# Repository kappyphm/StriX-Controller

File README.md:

# StriX Controller

The StriX Controller is a custom-designed game controller for flight simulation games, featuring dual analog joysticks, four switches, and a user-friendly USB Type-C interface. Built with an AtMega32U4 microcontroller, it supports HID protocol for plug-and-play compatibility. The controller includes an OLED display for real-time feedback via I2C and supports configuration through a rotary encoder (KY-040) or a software driver. Designed with modularity in mind, it includes an SPI interface for potential integration with the StriX UAV project via an NRF24L01 module.

## Features

- **Dual Analog Joysticks**: Precise control for flight simulation games.
- **Four Switches**: Additional input options for customizable actions.
- **USB Type-C Connectivity**: Modern, reliable connection for data and firmware updates.
- **AtMega32U4 MCU**: Provides native HID support for seamless integration with PCs.
- **OLED Display**: Displays real-time information via I2C communication.
- **Configurability**: Adjust settings using a KY-040 rotary encoder or a software driver.
- **SPI Interface**: Reserved pins for NRF24L01 module, enabling future StriX UAV integration.
- **Firmware Updates**: Update firmware via USB Type-C using standard tools like avrdude.

## Project Structure

- **Hardware/**: Contains KiCad project files for the controller’s PCB design and schematics.
- **Software/**: Placeholder for the software driver
- **Firmware/**: PlatformIO project for the AtMega32U4, including firmware code for controller functionality.

## Hardware Requirements

- AtMega32U4 microcontroller
- Dual analog joysticks
- Four switches
- USB Type-C port
- OLED display (I2C-compatible)
- KY-040 rotary encoder
- Optional: NRF24L01 module for future wireless expansion

## Setup Instructions

1. **Hardware Setup**:
   - Assemble the controller using the KiCad schematics in the `Hardware/` folder.
   - Ensure proper connections for the AtMega32U4, joysticks, switches, OLED, and KY-040.
2. **Firmware Installation**:
   - Clone the repository and open the `Firmware/` folder in PlatformIO.
   - Build and upload the firmware to the AtMega32U4 via USB Type-C using a compatible tool (e.g., avrdude).
3. **Software Driver**:
   - (TBD) Develop or install the driver from the `Software/` folder to configure controller settings.
4. **Testing**:
   - Connect the controller to a PC via USB Type-C.
   - Verify HID functionality and OLED display output.
   - Test joystick, switch, and KY-040 inputs in a flight simulation game.

## Firmware Updates

To update the firmware:

1. Connect the controller to a PC via USB Type-C.
2. Use a tool like avrdude to flash the updated firmware from the `Firmware/` folder.
3. Follow the PlatformIO documentation for detailed build and upload instructions.

## Future Expansion

The StriX Controller is designed for future integration with the StriX UAV project. The reserved SPI pins allow connection to an NRF24L01 module, enabling the controller to function as a transmitter (TX) for UAV control.

## Contributing

Contributions are welcome! Please fork the repository, make changes, and submit a pull request. Ensure your code follows the project’s coding standards and includes appropriate documentation.

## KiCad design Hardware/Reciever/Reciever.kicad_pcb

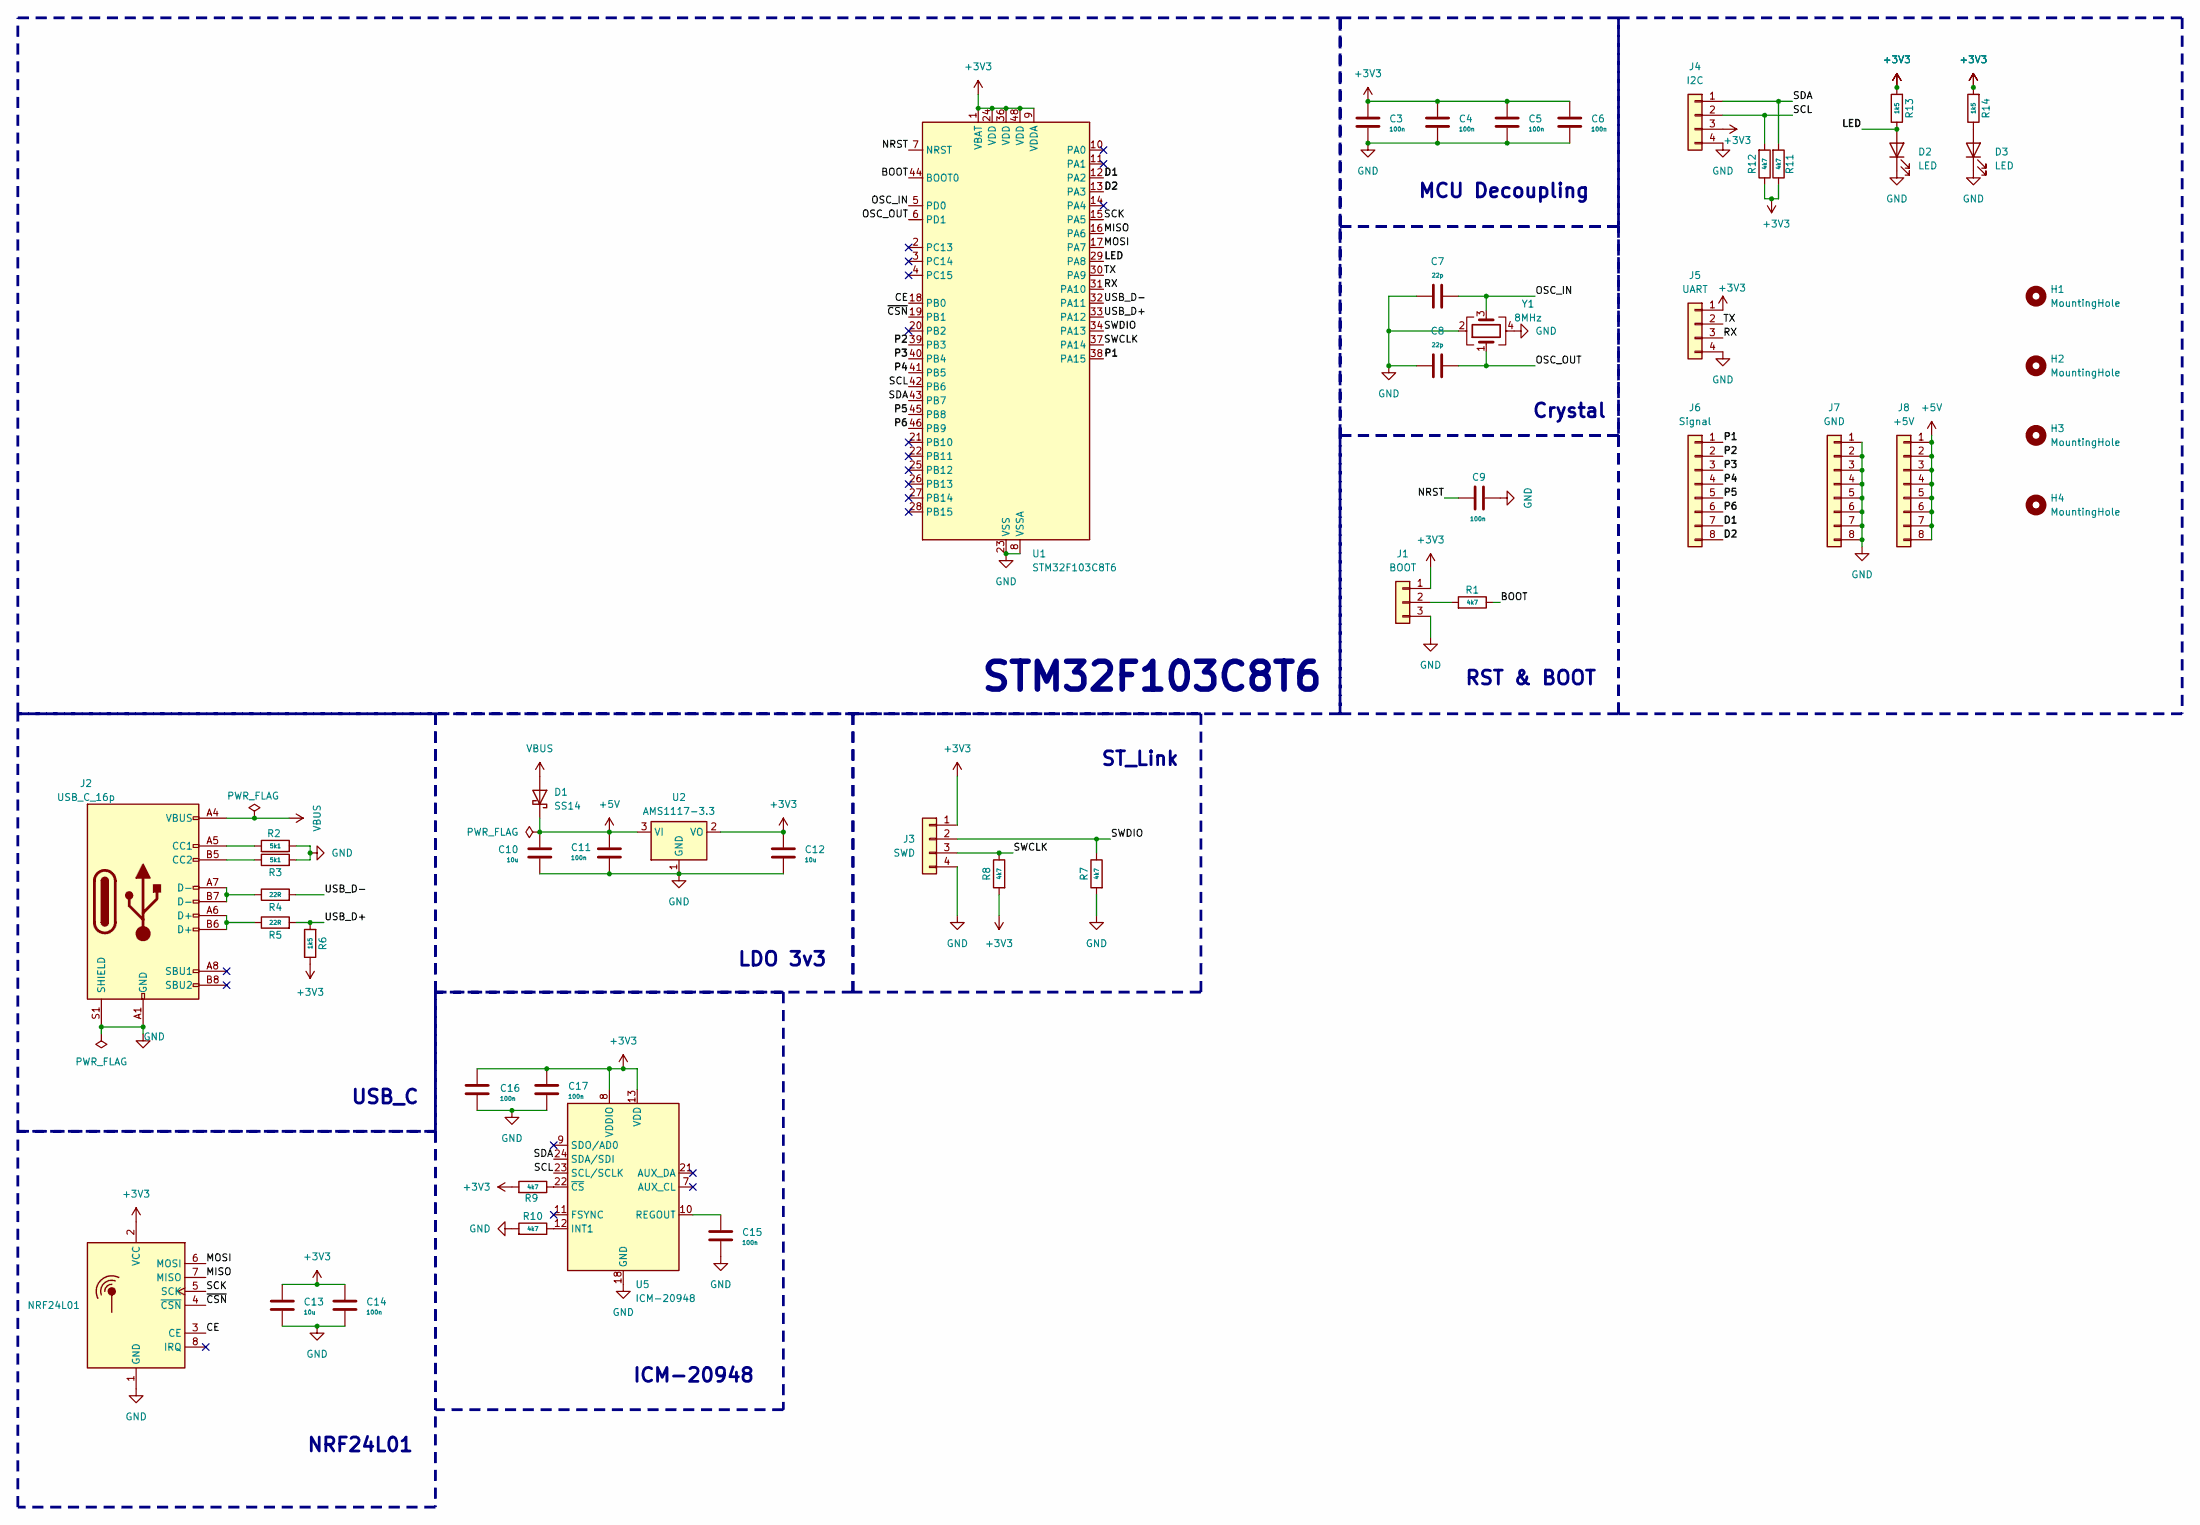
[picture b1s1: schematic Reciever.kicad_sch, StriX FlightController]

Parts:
C3, C4, C5, C6, C9, C11, C14, C15, C16, C17: 100n; C_0603_1608Metric
C7, C8: 22p; C_0603_1608Metric
C10, C12, C13: 10u; C_0603_1608Metric
D1: SS14; D_SMA
D2, D3: LED; LED_1206_3216Metric
H1, H2, H3, H4: MountingHole; MountingHole_2.5mm
J1: BOOT; PinHeader_1x03_P2.54mm_Vertical
J2: USB_C_16p; USB_C_Receptacle_HRO_TYPE-C-31-M-12
J3: SWD; PinHeader_1x04_P2.54mm_Vertical
J4: I2C; PinHeader_1x04_P2.54mm_Vertical
J5: UART; PinHeader_1x04_P2.54mm_Vertical
J6: Signal; PinHeader_1x08_P2.54mm_Vertical
J7: GND; PinHeader_1x08_P2.54mm_Vertical
J8: +5V; PinHeader_1x08_P2.54mm_Vertical
R1, R7, R8, R9, R10, R11, R12: 4k7; R_0603_1608Metric
R2, R3: 5k1; R_0603_1608Metric
R4, R5: 22R; R_0603_1608Metric
R6, R13, R14: 1k5; R_0603_1608Metric
U1: STM32F103C8T6; LQFP-48_7x7mm_P0.5mm
U2: AMS1117-3.3; SOT-223-3_TabPin2
U4: NRF24L01; NRF24L01_PA_LNA
U5: ICM-20948; InvenSense_QFN-24_3x3mm_P0.4mm
Y1: 8MHz; Crystal_SMD_5032-4Pin_5.0x3.2mm

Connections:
+3V3: C3.1, C4.1, C5.1, C6.1, C12.1, C13.1, C14.1, C16.1, C17.1, J1.1, J3.1, J4.3, J5.1, R6.1, R8.2, R9.2, R11.1, R12.1, R13.2, R14.2, U1.1 (VBAT), U1.9 (VDDA), U1.24 (VDD), U1.36 (VDD), U1.48 (VDD), U2.2 (VO), U4.2 (VCC), U5.8 (VDDIO), U5.13 (VDD)
+5V: C10.1, C11.1, D1.1 (K), J8.1, J8.2, J8.3, J8.4, J8.5, J8.6, J8.7, J8.8, U2.3 (VI)
/BOOT: R1.1, U1.44 (BOOT0)
/CE: U1.18 (PB0), U4.3 (CE)
/D1: J6.7, U1.12 (PA2)
/D2: J6.8, U1.13 (PA3)
/LED: D2.2 (A), R13.1, U1.29 (PA8)
/MISO: U1.16 (PA6), U4.7 (MISO)
/MOSI: U1.17 (PA7), U4.6 (MOSI)
/NRST: C9.1, U1.7 (NRST)
/OSC_IN: C7.2, U1.5 (PD0), Y1.3
/OSC_OUT: C8.2, U1.6 (PD1), Y1.1
/P1: J6.1, U1.38 (PA15)
/P2: J6.2, U1.39 (PB3)
/P3: J6.3, U1.40 (PB4)
/P4: J6.4, U1.41 (PB5)
/P5: J6.5, U1.45 (PB8)
/P6: J6.6, U1.46 (PB9)
/RX: J5.3, U1.31 (PA10)
/SCK: U1.15 (PA5), U4.5 (SCK)
/SCL: J4.2, R12.2, U1.42 (PB6), U5.23 (SCL/SCLK)
/SDA: J4.1, R11.2, U1.43 (PB7), U5.24 (SDA/SDI)
/SWCLK: J3.3, R8.1, U1.37 (PA14)
/SWDIO: J3.2, R7.1, U1.34 (PA13)
/TX: J5.2, U1.30 (PA9)
/USB_D+: R5.2, R6.2, U1.33 (PA12)
/USB_D-: R4.2, U1.32 (PA11)
/~CSN: U1.19 (PB1), U4.4 (~CSN)
GND: C3.2, C4.2, C5.2, C6.2, C7.1, C8.1, C9.2, C10.2, C11.2, C12.2, C13.2, C14.2, C15.2, C16.2, C17.2, D2.1 (K), D3.1 (K), J1.3, J2.A1 (GND), J2.A12 (GND), J2.B1 (GND), J2.B12 (GND), J2.S1 (SHIELD), J3.4, J4.4, J5.4, J7.1, J7.2, J7.3, J7.4, J7.5, J7.6, J7.7, J7.8, R2.2, R3.2, R7.2, R10.2, U1.8 (VSSA), U1.23 (VSS), U1.35 (VSS), U1.47 (VSS), U2.1 (GND), U4.1 (GND), U5.18 (GND), U5.20 (GND), Y1.2, Y1.4
unnamed: D3.2 (A), R14.1
unnamed: J1.2, R1.2
unnamed: J2.A5 (CC1), R2.1
unnamed: J2.B5 (CC2), R3.1
unnamed: J2.A6 (D+), J2.B6 (D+), R5.1
unnamed: J2.A7 (D-), J2.B7 (D-), R4.1
unnamed: R10.1, U5.12 (INT1)
unnamed: C15.1, U5.10 (REGOUT)
unnamed: R9.1, U5.22 (~CS)
VBUS: D1.2 (A), J2.A4 (VBUS), J2.A9 (VBUS), J2.B4 (VBUS), J2.B9 (VBUS)

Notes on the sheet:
ST_Link
Crystal
LDO 3v3
USB_C
ICM-20948
RST & BOOT
NRF24L01
STM32F103C8T6
MCU Decoupling

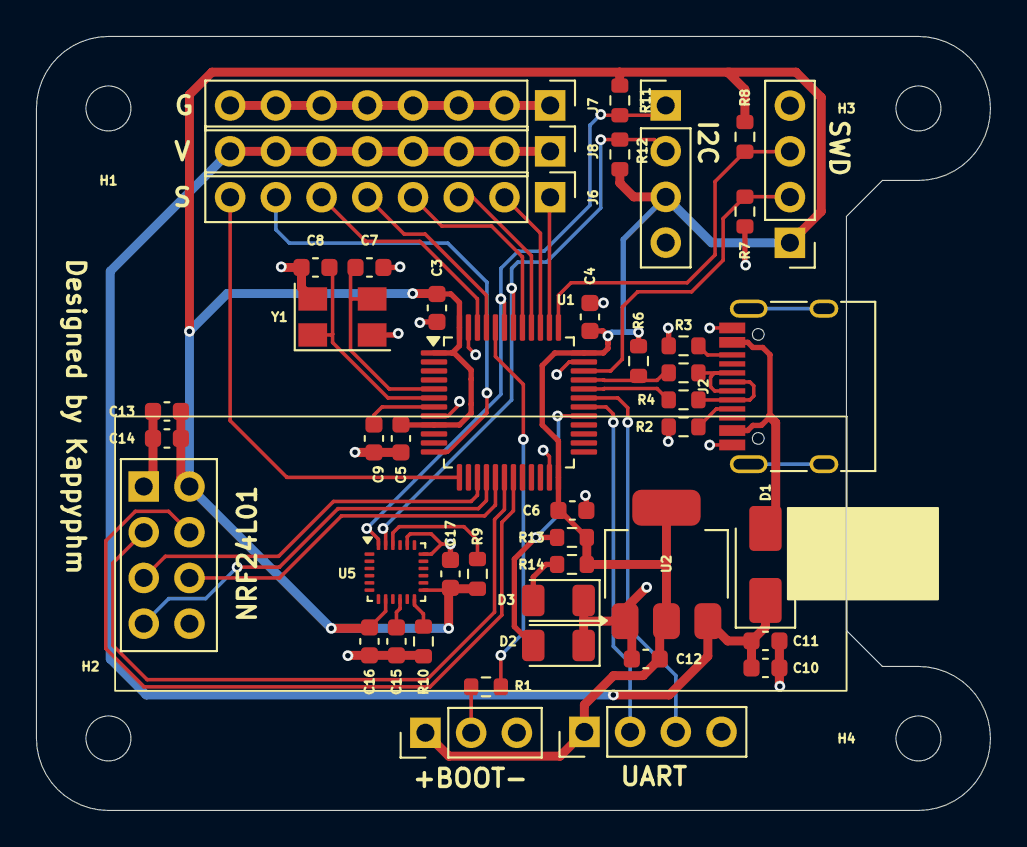
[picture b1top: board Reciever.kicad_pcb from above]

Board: 2 copper layers, 53.0 x 43.0 mm, 49 parts (0 on the bottom side), 39 nets.

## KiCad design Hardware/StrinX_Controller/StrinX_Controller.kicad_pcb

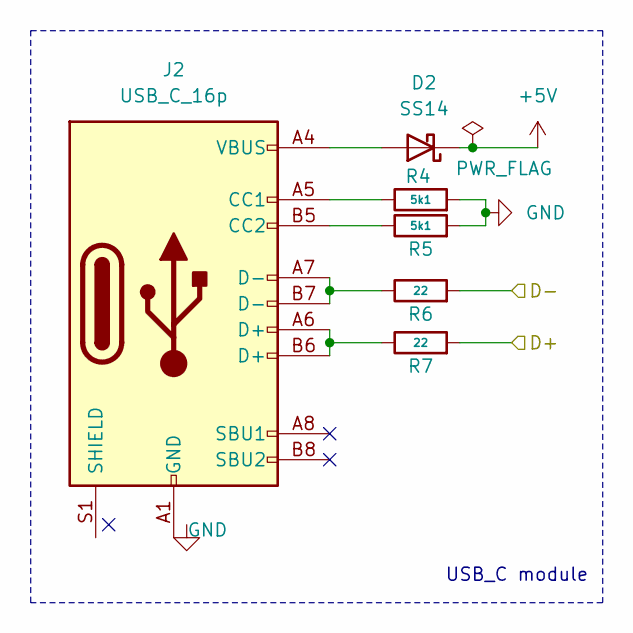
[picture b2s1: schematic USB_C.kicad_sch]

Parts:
D2: SS14; D_SMA
J2: USB_C_16p
R4, R5: 5k1
R6, R7: 22

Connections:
+5V: D2.1 (K); also elsewhere on the board
/AT32u4/D+: R7.2; also elsewhere on the board
/AT32u4/D-: R6.2; also elsewhere on the board
unnamed: D2.2 (A), J2.A4 (VBUS), J2.A9 (VBUS), J2.B4 (VBUS), J2.B9 (VBUS)
unnamed: J2.A5 (CC1), R4.1
unnamed: J2.B5 (CC2), R5.1
unnamed: J2.A6 (D+), J2.B6 (D+), R7.1
unnamed: J2.A7 (D-), J2.B7 (D-), R6.1

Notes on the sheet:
USB_C module

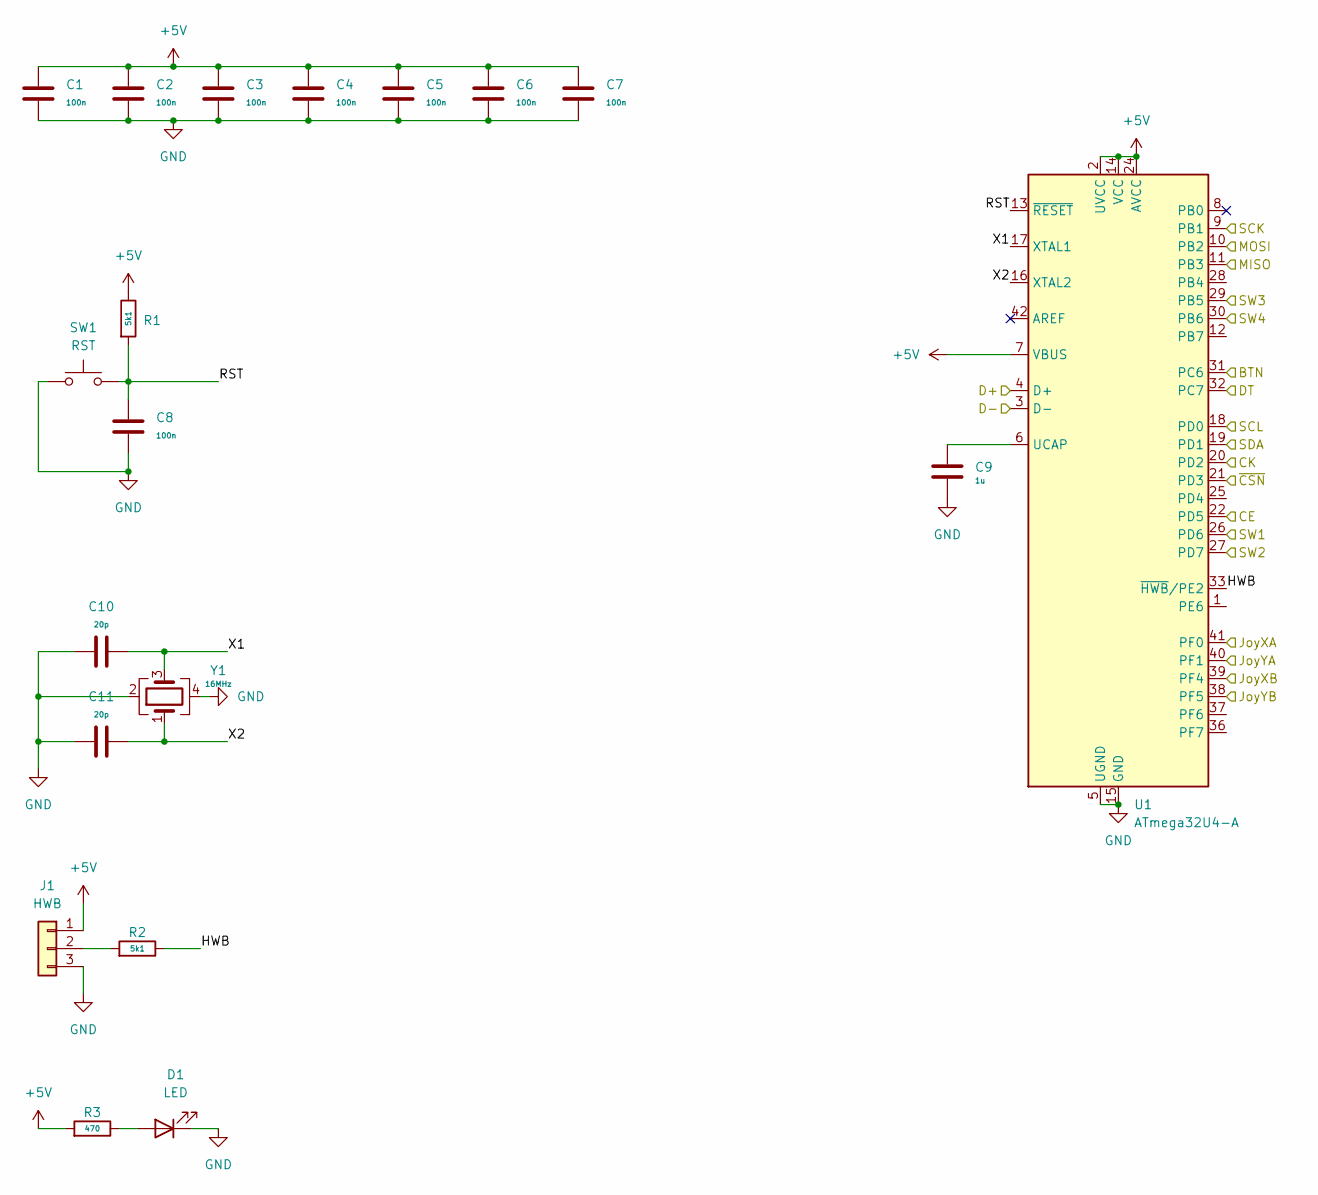
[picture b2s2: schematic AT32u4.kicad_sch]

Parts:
C1, C2, C3, C4, C5, C6, C7, C8: 100n; C_0603_1608Metric
C9: 1u; C_0603_1608Metric
C10, C11: 20p; C_0603_1608Metric
D1: LED; LED_1206_3216Metric
J1: HWB; PinHeader_1x03_P2.54mm_Vertical
R1, R2: 5k1; R_0603_1608Metric
R3: 470; R_0603_1608Metric
SW1: RST; SW_PUSH_6mm_H4.3mm
U1: ATmega32U4-A; TQFP-44_10x10mm_P0.8mm
Y1: 16MHz; Crystal_SMD_7050-4Pin_7.0x5.0mm

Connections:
+5V: C1.1, C2.1, C3.1, C4.1, C5.1, C6.1, C7.1, J1.1, R1.1, R3.2, U1.2 (UVCC), U1.7 (VBUS), U1.14 (VCC), U1.24 (AVCC), U1.34 (VCC), U1.44 (AVCC); also elsewhere on the board
/AT32u4/BTN: U1.31 (PC6); also elsewhere on the board
/AT32u4/CE: U1.22 (PD5); also elsewhere on the board
/AT32u4/CK: U1.20 (PD2); also elsewhere on the board
/AT32u4/D+: U1.4 (D+); also elsewhere on the board
/AT32u4/D-: U1.3 (D-); also elsewhere on the board
/AT32u4/DT: U1.32 (PC7); also elsewhere on the board
/AT32u4/HWB: R2.1, U1.33 (~HWB/PE2)
/AT32u4/JoyXA: U1.41 (PF0); also elsewhere on the board
/AT32u4/JoyXB: U1.39 (PF4); also elsewhere on the board
/AT32u4/JoyYA: U1.40 (PF1); also elsewhere on the board
/AT32u4/JoyYB: U1.38 (PF5); also elsewhere on the board
/AT32u4/MISO: U1.11 (PB3); also elsewhere on the board
/AT32u4/MOSI: U1.10 (PB2); also elsewhere on the board
/AT32u4/RST: C8.1, R1.2, SW1.2, U1.13 (~RESET)
/AT32u4/SCK: U1.9 (PB1); also elsewhere on the board
/AT32u4/SCL: U1.18 (PD0); also elsewhere on the board
/AT32u4/SDA: U1.19 (PD1); also elsewhere on the board
/AT32u4/SW1: U1.26 (PD6); also elsewhere on the board
/AT32u4/SW2: U1.27 (PD7); also elsewhere on the board
/AT32u4/SW3: U1.29 (PB5); also elsewhere on the board
/AT32u4/SW4: U1.30 (PB6); also elsewhere on the board
/AT32u4/X1: C10.2, U1.17 (XTAL1), Y1.3
/AT32u4/X2: C11.2, U1.16 (XTAL2), Y1.1
/AT32u4/~CSN: U1.21 (PD3); also elsewhere on the board
unnamed: D1.2 (A), R3.1
unnamed: J1.2, R2.2
unnamed: C9.2, U1.6 (UCAP)

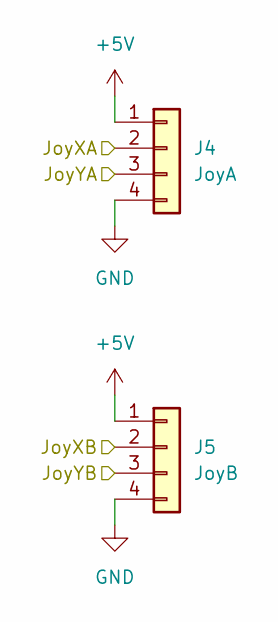
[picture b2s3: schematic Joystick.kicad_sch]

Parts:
J4: JoyA; PinHeader_1x04_P2.54mm_Vertical
J5: JoyB; PinHeader_1x04_P2.54mm_Vertical

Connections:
+5V: J4.1, J5.1; also elsewhere on the board
/AT32u4/JoyXA: J4.2; also elsewhere on the board
/AT32u4/JoyXB: J5.2; also elsewhere on the board
/AT32u4/JoyYA: J4.3; also elsewhere on the board
/AT32u4/JoyYB: J5.3; also elsewhere on the board

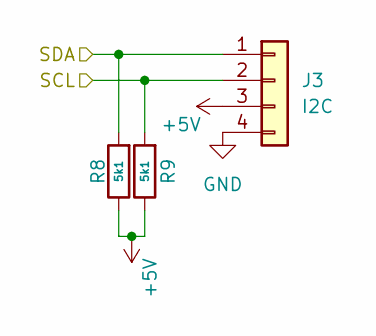
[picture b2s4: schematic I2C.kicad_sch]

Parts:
J3: I2C; PinHeader_1x04_P2.54mm_Vertical
R8, R9: 5k1; R_0603_1608Metric

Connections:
+5V: J3.3, R8.1, R9.1; also elsewhere on the board
/AT32u4/SCL: J3.2, R9.2; also elsewhere on the board
/AT32u4/SDA: J3.1, R8.2; also elsewhere on the board

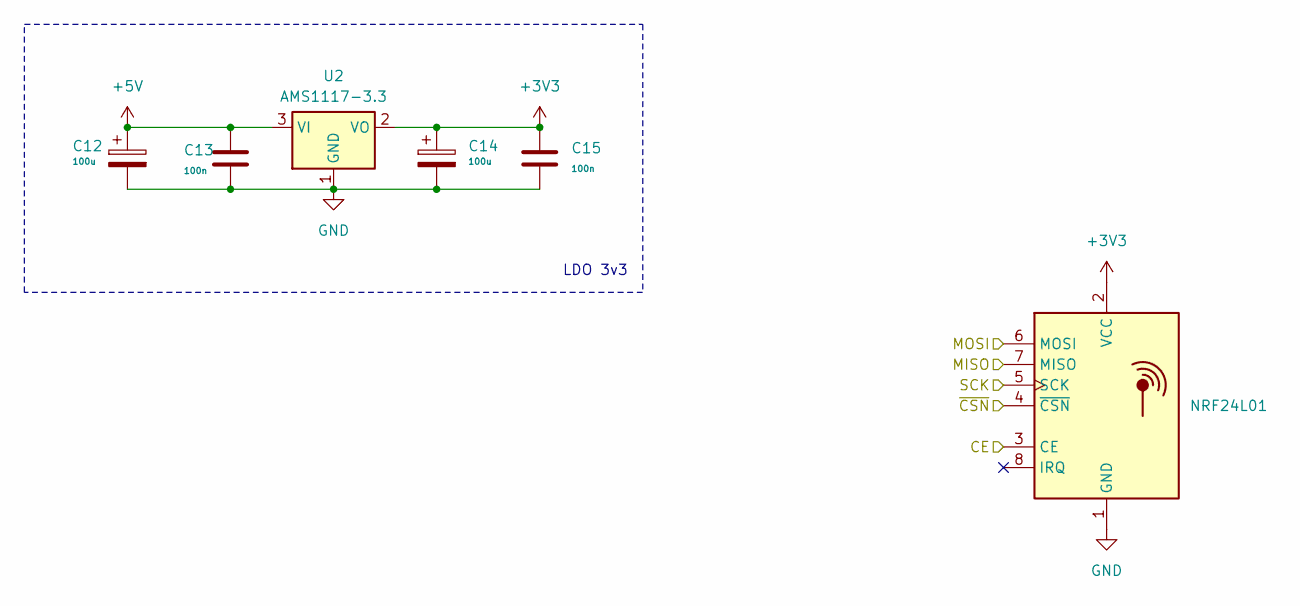
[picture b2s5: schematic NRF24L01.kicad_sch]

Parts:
C12, C14: 100u; C_Radial_D8.0mm_H11.5mm_P3.50mm
C13, C15: 100n; C_0603_1608Metric
U2: AMS1117-3.3; SOT-223-3_TabPin2
U3: NRF24L01; NRF24L01_PA_LNA

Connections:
+3V3: C14.1, C15.1, U2.2 (VO), U3.2 (VCC)
+5V: C12.1, C13.1, U2.3 (VI); also elsewhere on the board
/AT32u4/CE: U3.3 (CE); also elsewhere on the board
/AT32u4/MISO: U3.7 (MISO); also elsewhere on the board
/AT32u4/MOSI: U3.6 (MOSI); also elsewhere on the board
/AT32u4/SCK: U3.5 (SCK); also elsewhere on the board
/AT32u4/~CSN: U3.4 (~CSN); also elsewhere on the board

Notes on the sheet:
LDO 3v3

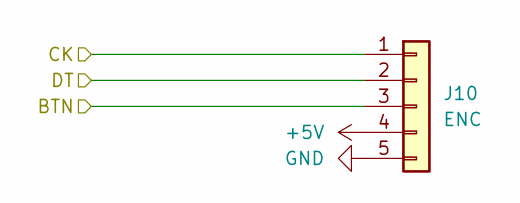
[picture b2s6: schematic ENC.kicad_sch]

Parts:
J10: ENC; PinHeader_1x05_P2.54mm_Vertical

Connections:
+5V: J10.4; also elsewhere on the board
/AT32u4/BTN: J10.3; also elsewhere on the board
/AT32u4/CK: J10.1; also elsewhere on the board
/AT32u4/DT: J10.2; also elsewhere on the board

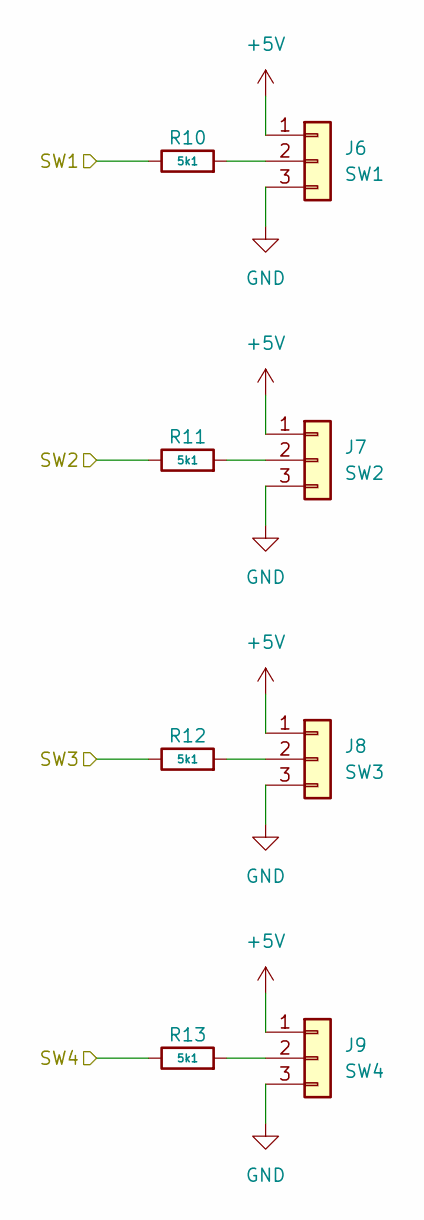
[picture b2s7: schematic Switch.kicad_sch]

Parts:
J6: SW1; PinHeader_1x03_P2.54mm_Vertical
J7: SW2; PinHeader_1x03_P2.54mm_Vertical
J8: SW3; PinHeader_1x03_P2.54mm_Vertical
J9: SW4; PinHeader_1x03_P2.54mm_Vertical
R10, R11, R12, R13: 5k1; R_0603_1608Metric

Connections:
+5V: J6.1, J7.1, J8.1, J9.1; also elsewhere on the board
/AT32u4/SW1: R10.1; also elsewhere on the board
/AT32u4/SW2: R11.1; also elsewhere on the board
/AT32u4/SW3: R12.1; also elsewhere on the board
/AT32u4/SW4: R13.1; also elsewhere on the board
unnamed: J6.2, R10.2
unnamed: J7.2, R11.2
unnamed: J8.2, R12.2
unnamed: J9.2, R13.2

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
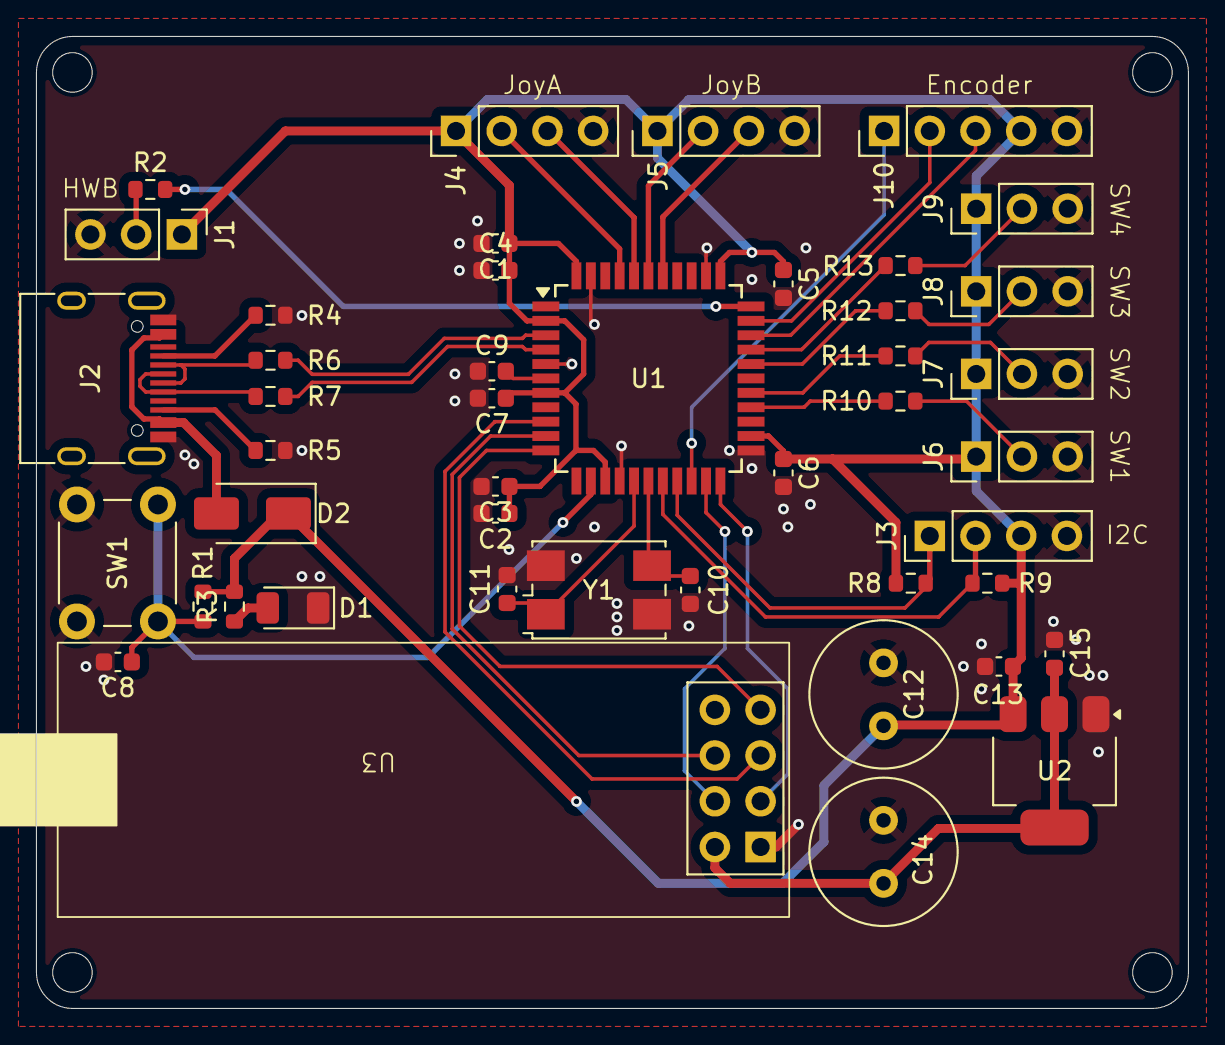
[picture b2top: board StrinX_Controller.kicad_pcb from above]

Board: 2 copper layers, 64.0 x 54.0 mm, 45 parts (0 on the bottom side), 39 nets.

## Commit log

2025-07-29 init hardware
2025-07-29 Add ATmega32U4 schematic and update project files
    Added AT32u4.kicad_sch schematic for the ATmega32U4 microcontroller. Updated StrinX_Controller.kicad_pro and StrinX_Controller.kicad_sch to include the new schematic and related changes for hardware 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
2025-07-29 Add new input pins to StrinX_Controller schematic
    Expanded the StrinX_Controller.kicad_sch sheet size and added multiple new input pins for various signals (JoyXA, JoyYA, JoyXB, JoyYB, SW1-SW4, BTN, CK, DT, SCL, SDA, SPI, USB, etc.). Also updated AT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
2025-07-29 Add USB-C schematic module
2025-07-29 Add NRF24L01 module
2025-07-29 Fix merge error
2025-07-29 Add device and footprint
2025-07-30 Update BOM file
2025-07-30 Init PCB
2025-07-30 Add some capacitor for MCU
2025-07-30 Update some device connection and Complete PCB
2025-07-30 Done merge
2025-07-30 Fix ERC error
2025-07-30 Export
2025-08-05 Add receiver hardware
    Initial commit of KiCad schematic and PCB files for the receiver hardware, including MCU, NRF24L01, sensor, USB-C, and project configuration files.
2025-08-05 Fix layout
2025-08-05 remove smt
2025-08-05 Remove trash
